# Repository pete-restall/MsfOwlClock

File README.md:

# MSF Owl Clock
<span style="display:block;text-align:center"></span>

The board with the ferrite rod antenna and two TFT displays attached.

The above images are the boards as delivered from fabrication, not the end product.  Namely:
* The edge / tool rails need to be cut off to leave only the owl-shaped board
* A ferrite rod antenna (and tuning capacitors) need to be attached, creating a branch on which the owl perches (yellow tie-wraps for talons)
* Two TFT displays need to be secured in place for the eyes
* A base / stand needs to be 3D printed, which will also hold a speaker and its cavity

This project is a desk clock intended to synchronise with the [60kHz AM MSF](doc/datasheets/msf/msf.pdf) time signal that is broadcast by the UK's NPL using their [Anthorn Radio Station in Cumbria, England](https://www.npl.co.uk/msf-signal).

The [board schematics](src/schematics/msf-owl-clock.pdf) and [PCB fab files](src/pcb-fab/) were created in KiCAD.  [Firmware](src/firmware/) will, no doubt, be a very long-running part of the project (as usually seems to happen...)

The board consists of:
* A [PIC32CX1025SG41100](doc/datasheets/mcu/PIC32CX1025SG41100-datasheet-DS60001715.pdf) ARM Cortex M4F:
  * M-profile ARM v7 CPU running up to 120MHz
  * 1MiB flash
  * 256KiB SRAM
  * 8KiB backup SRAM
  * 1Msps 12-bit ADC
  * 1Msps 12-bit DAC
* Two multiplexed QSPI [360x360 Circular TFTs](doc/datasheets/tft/buydisplay-ER-TFT1.32-1.pdf) for the eyes
* A USB Type-C connector with USB PD / charger detection and USB2.0 Full Speed data
* A Micro SD Card connector
* An [IS31AP4991A](doc/datasheets/opamps/IS31AP4991A-SLS2-TR.pdf) audio amplifier / speaker driver (the speaker and cavity will be built into a 3D-printed base / stand)
* A [BC805M](doc/datasheets/bluetooth/BC805M.pdf) 2.4GHz Bluetooth / BLE 5.2 Module running an [nRF52805](doc/datasheets/bluetooth/nRF52805_PS_v1.4.pdf) ARM Cortex M4
* A range of I<sup>2</sup>C sensors:
  * A [DPS310XTSA1](doc/datasheets/sensors/pressure/DPS310XTSA1.pdf) Pressure Sensor to create a barometer
  * A [HDC3022](doc/datasheets/sensors/humidity/HDC3022.pdf) Humidity Sensor for measuring humidity and temperature
  * A [VL6180V1NR](doc/datasheets/sensors/proximity/VL6180V1NR-1.pdf) Proximity Sensor to allow power-saving mode when nobody is nearby / at night
  * A [TSOP75338TT](doc/datasheets/sensors/infrared/TSOP75338TT.pdf) 38kHz Infrared Receiver to allow remote control

The board is shaped as an owl as it is intended for my daughter, a little girl that _really_ likes owls.  I hope it will spark some curiosity and prompt her to enquire how everyday items and systems around her work, things that most people take for granted or do not even notice.

Obviously it's also for me to play with, as and when I get the time.

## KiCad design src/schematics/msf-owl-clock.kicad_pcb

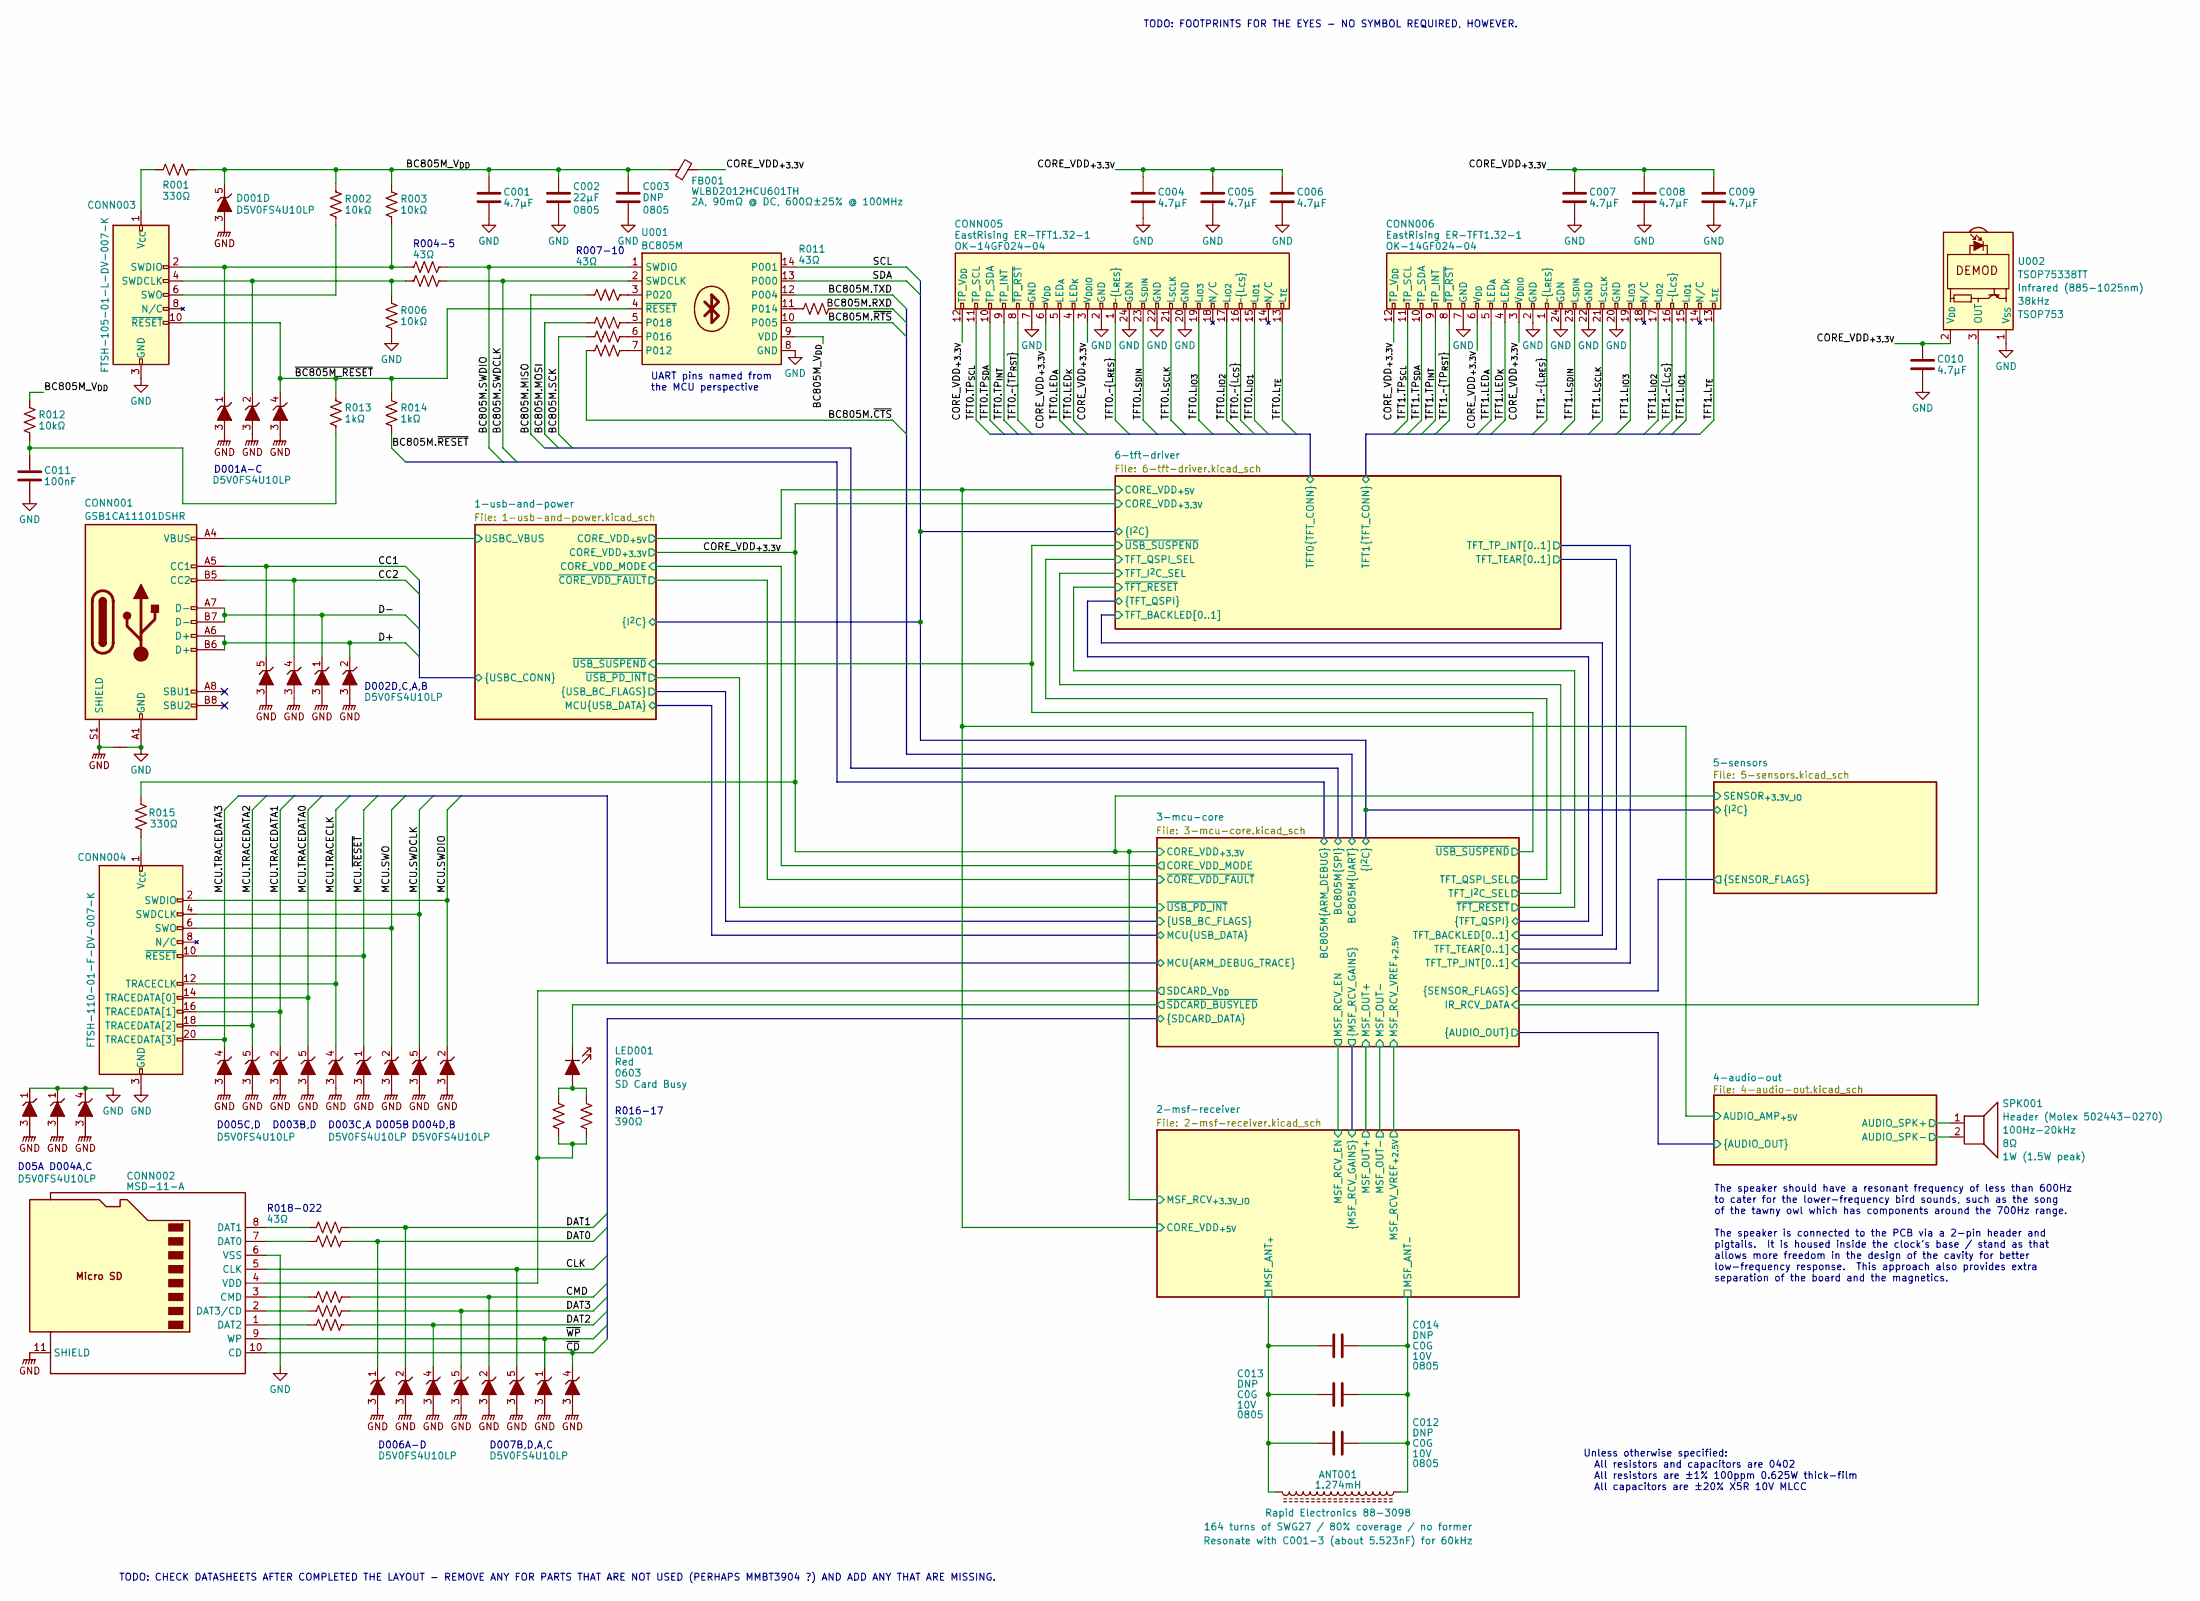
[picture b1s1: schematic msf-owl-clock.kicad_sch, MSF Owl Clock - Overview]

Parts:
ANT001: 1.274mH; ferrite-rod-antenna; ManufacturerPartNumber Rapid Electronics 88-3098
C001, C004, C005, C006, C007, C008, C009, C010: 4.7μF; unpolarised-nominal-0402-1005; Tolerance ±20%; VoltageRating 10V; ManufacturerPartNumber CL05A475MP5NRNC
C002: 22μF; unpolarised-nominal-0805-2012; Tolerance ±20%; VoltageRating 10V; ManufacturerPartNumber CL21A226MPQNNN
C003: DNP; unpolarised-nominal-0805-2012; Tolerance ±20%; VoltageRating 10V; ManufacturerPartNumber CL21A226MPQNNN
C011: 100nF; unpolarised-nominal-0402-1005; Tolerance ±20%; VoltageRating 10V; ManufacturerPartNumber CL05B104KA5NNNC
C012, C013, C014: DNP; unpolarised-nominal-0805-2012; VoltageRating 10V
CONN001: GSB1CA11101DSHR; ManufacturerPartNumber GSB1CA11101DSHR
CONN002: MSD-11-A; ManufacturerPartNumber MSD-11-A
CONN003: Cortex-M Debug Header; FTSH-105-?-?-DV-007-?-?; ManufacturerPartNumber FTSH-105-01-L-DV-007-K
CONN004: Cortex-M Debug Header with ETM; FTSH-110-01-?-DV-007-?-?; ManufacturerPartNumber FTSH-110-01-F-DV-007-K
CONN005, CONN006: EastRising ER-TFT1.32-1; OK-14GF024-04; ManufacturerPartNumber OK-14GF024-04
D001, D002, D003, D004, D005, D006, D007: D5V0FS4U10LP; ManufacturerPartNumber D5V0FS4U10LP
FB001: WLBD2012HCU601TH; WLBD2012; Tolerance ±25%; ManufacturerPartNumber WLBD2012HCU601TH
LED001: SD Card Busy; nominal-0603-1608; ManufacturerPartNumber B1931USD-20D000814U1930
NT001: Net Tie; net-tie-2-6mil
R001, R015: 330Ω; nominal-0402-1005; Tolerance ±1%; ManufacturerPartNumber WR04X3300FTL
R002, R003, R006, R012: 10kΩ; nominal-0402-1005; Tolerance ±1%; ManufacturerPartNumber WR04X1002FTL
R004, R005, R007, R008, R009, R010, R011, R018, R019, R020, R021, R022: 43Ω; nominal-0402-1005; Tolerance ±1%; ManufacturerPartNumber RC0402FR-0743RL
R013, R014: 1kΩ; nominal-0402-1005; Tolerance ±1%; ManufacturerPartNumber WR04X1001FTL
R016, R017: 390Ω; nominal-0402-1005; Tolerance ±1%; ManufacturerPartNumber RC0402FR-07390RL
SHEET001, SHEET002, SHEET003, SHEET004, SHEET005, SHEET006: (no value)
SPK001: Header (Molex 502443-0270); 502443-0270; Rating 1W (1.5W peak); ManufacturerPartNumber AC0402DR-0716KL
U001: BC805M; ManufacturerPartNumber BC805M
U002: TSOP75338TT; TSOP7????TT; ManufacturerPartNumber TSOP75338TT

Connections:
/1-usb-and-power/CC1: CONN001.A5 (CC1), D002.5 (K), D002.6; also elsewhere on the board
/1-usb-and-power/CC2: CONN001.B5 (CC2), D002.4 (K), D002.7; also elsewhere on the board
/1-usb-and-power/CORE_VDD_{+5V}: CONN005.5 (LED_{A}), CONN006.5 (LED_{A}); also elsewhere on the board
/1-usb-and-power/D+: CONN001.A6 (D+), CONN001.B6 (D+), D002.2 (K), D002.9; also elsewhere on the board
/1-usb-and-power/D-: CONN001.A7 (D-), CONN001.B7 (D-), D002.1 (K), D002.10; also elsewhere on the board
/1-usb-and-power/SCL: U001.14 (P001); also elsewhere on the board
/1-usb-and-power/SDA: U001.13 (P000); also elsewhere on the board
/1-usb-and-power/USBC_VBUS: CONN001.A4 (VBUS), CONN001.A9 (VBUS), CONN001.B4 (VBUS), CONN001.B9 (VBUS); also elsewhere on the board
/2-msf-receiver/MSF_ANT_{+}: ANT001.1, C012.1, C013.1, C014.1; also elsewhere on the board
/2-msf-receiver/MSF_RCV_VREF_{+1.8V}: ANT001.2, C012.2, C013.2, C014.2; also elsewhere on the board
/3-mcu-core/BC805M.MISO: R007.1; also elsewhere on the board
/3-mcu-core/BC805M.MOSI: R008.1; also elsewhere on the board
/3-mcu-core/BC805M.RXD: R011.2; also elsewhere on the board
/3-mcu-core/BC805M.SCK: R009.1; also elsewhere on the board
/3-mcu-core/BC805M.SWDCLK: R005.2, U001.2 (SWDCLK); also elsewhere on the board
/3-mcu-core/BC805M.SWDIO: R004.2, U001.1 (SWDIO); also elsewhere on the board
/3-mcu-core/BC805M.TXD: U001.12 (P004); also elsewhere on the board
/3-mcu-core/BC805M.~CTS: R010.1; also elsewhere on the board
/3-mcu-core/BC805M.~RESET: R014.2; also elsewhere on the board
/3-mcu-core/BC805M.~RTS: U001.10 (P005); also elsewhere on the board
/3-mcu-core/CLK: CONN002.5 (CLK), D007.5 (K), D007.6; also elsewhere on the board
/3-mcu-core/CMD: D007.2 (K), D007.9, R020.2; also elsewhere on the board
/3-mcu-core/DAT0: D006.1 (K), D006.10, R019.2; also elsewhere on the board
/3-mcu-core/DAT1: D006.2 (K), D006.9, R018.2; also elsewhere on the board
/3-mcu-core/DAT2: D006.4 (K), D006.7, R022.2; also elsewhere on the board
/3-mcu-core/DAT3: D006.5 (K), D006.6, R021.2; also elsewhere on the board
/3-mcu-core/IR_RCV_DATA: U002.3 (OUT); also elsewhere on the board
/3-mcu-core/MCU.SWDCLK: CONN004.4 (SWDCLK), D004.5 (K), D004.6; also elsewhere on the board
/3-mcu-core/MCU.SWDIO: CONN004.2 (SWDIO), D004.2 (K), D004.9; also elsewhere on the board
/3-mcu-core/MCU.SWO: CONN004.6 (SWO), D005.2 (K), D005.9; also elsewhere on the board
/3-mcu-core/MCU.TRACECLK: CONN004.12 (TRACECLK), D003.4 (K), D003.7; also elsewhere on the board
/3-mcu-core/MCU.TRACEDATA0: CONN004.14 (TRACEDATA[0]), D003.5 (K), D003.6; also elsewhere on the board
/3-mcu-core/MCU.TRACEDATA1: CONN004.16 (TRACEDATA[1]), D003.2 (K), D003.9; also elsewhere on the board
/3-mcu-core/MCU.TRACEDATA2: CONN004.18 (TRACEDATA[2]), D005.5 (K), D005.6; also elsewhere on the board
/3-mcu-core/MCU.TRACEDATA3: CONN004.20 (TRACEDATA[3]), D005.4 (K), D005.7; also elsewhere on the board
/3-mcu-core/MCU.~RESET: CONN004.10 (~RESET), D003.1 (K), D003.10; also elsewhere on the board
/3-mcu-core/SDCARD_V_{DD}: CONN002.4 (VDD), R016.2, R017.2; also elsewhere on the board
/3-mcu-core/~CD: CONN002.10 (CD), D007.4 (K), D007.7; also elsewhere on the board
/3-mcu-core/~SDCARD_BUSYLED: LED001.1 (K); also elsewhere on the board
/3-mcu-core/~WP: CONN002.9 (WP), D007.1 (K), D007.10; also elsewhere on the board
/4-audio-out/AUDIO_SPK+: SPK001.1; also elsewhere on the board
/4-audio-out/AUDIO_SPK-: SPK001.2; also elsewhere on the board
/6-tft-driver/TFT0.LED_{K}: CONN005.4 (LED_{K}); also elsewhere on the board
/6-tft-driver/TFT0.L_{IO1}: CONN005.15 (L_{IO1}); also elsewhere on the board
/6-tft-driver/TFT0.L_{IO2}: CONN005.17 (L_{IO2}); also elsewhere on the board
/6-tft-driver/TFT0.L_{IO3}: CONN005.19 (L_{IO3}); also elsewhere on the board
/6-tft-driver/TFT0.L_{SCLK}: CONN005.21 (L_{SCLK}); also elsewhere on the board
/6-tft-driver/TFT0.L_{SDIN}: CONN005.23 (L_{SDIN}); also elsewhere on the board
/6-tft-driver/TFT0.L_{TE}: CONN005.13 (L_{TE}); also elsewhere on the board
/6-tft-driver/TFT0.TP_{INT}: CONN005.9 (TP_INT); also elsewhere on the board
/6-tft-driver/TFT0.TP_{SCL}: CONN005.11 (TP_SCL); also elsewhere on the board
/6-tft-driver/TFT0.TP_{SDA}: CONN005.10 (TP_SDA); also elsewhere on the board
/6-tft-driver/TFT0.~L_{CS}: CONN005.16 (~L_{CS}); also elsewhere on the board
/6-tft-driver/TFT0.~L_{RES}: CONN005.1 (~L_{RES}); also elsewhere on the board
/6-tft-driver/TFT0.~TP_{RST}: CONN005.8 (~TP_RST); also elsewhere on the board
/6-tft-driver/TFT1.LED_{K}: CONN006.4 (LED_{K}); also elsewhere on the board
/6-tft-driver/TFT1.L_{IO1}: CONN006.15 (L_{IO1}); also elsewhere on the board
/6-tft-driver/TFT1.L_{IO2}: CONN006.17 (L_{IO2}); also elsewhere on the board
/6-tft-driver/TFT1.L_{IO3}: CONN006.19 (L_{IO3}); also elsewhere on the board
/6-tft-driver/TFT1.L_{SCLK}: CONN006.21 (L_{SCLK}); also elsewhere on the board
/6-tft-driver/TFT1.L_{SDIN}: CONN006.23 (L_{SDIN}); also elsewhere on the board
/6-tft-driver/TFT1.L_{TE}: CONN006.13 (L_{TE}); also elsewhere on the board
/6-tft-driver/TFT1.TP_{INT}: CONN006.9 (TP_INT); also elsewhere on the board
/6-tft-driver/TFT1.TP_{SCL}: CONN006.11 (TP_SCL); also elsewhere on the board
/6-tft-driver/TFT1.TP_{SDA}: CONN006.10 (TP_SDA); also elsewhere on the board
/6-tft-driver/TFT1.~L_{CS}: CONN006.16 (~L_{CS}); also elsewhere on the board
/6-tft-driver/TFT1.~L_{RES}: CONN006.1 (~L_{RES}); also elsewhere on the board
/6-tft-driver/TFT1.~TP_{RST}: CONN006.8 (~TP_RST); also elsewhere on the board
/BC805M_V_{DD}: C001.1, C002.1, C003.1, D001.5 (K), D001.6, FB001.1 (P1_PWROUT), R001.2, R002.1, R003.1, R012.1, U001.9 (VDD)
/CORE_VDD_{+3.3V}: C004.1, C005.1, C006.1, C007.1, C008.1, C009.1, C010.1, CONN005.3 (V_{DDIO}), CONN005.6 (V_{DD}), CONN005.12 (TP_V_{DD}), CONN006.3 (V_{DDIO}), CONN006.6 (V_{DD}), CONN006.12 (TP_V_{DD}), FB001.2 (P2_PWRIN), R015.2, U002.2 (V_{DD}); also elsewhere on the board
/~BC805M_RESET: CONN003.10 (~RESET), D001.4 (K), D001.7, R013.1, R014.1, U001.4 (~RESET)
unnamed: C011.1, R012.2, R013.2
unnamed: CONN002.3 (CMD), R020.1
unnamed: CONN002.7 (DAT0), R019.1
unnamed: CONN002.8 (DAT1), R018.1
unnamed: CONN002.1 (DAT2), R022.1
unnamed: CONN002.2 (DAT3/CD), R021.1
unnamed: CONN003.4 (SWDCLK), D001.2 (K), D001.9, R005.1, R006.1
unnamed: CONN003.2 (SWDIO), D001.1 (K), D001.10, R003.2, R004.1
unnamed: CONN003.6 (SWO), R002.2
unnamed: CONN003.1 (V_{CC}), R001.1
unnamed: CONN004.1 (V_{CC}), R015.1
unnamed: LED001.2 (A), R016.1, R017.1
unnamed: R010.2, U001.7 (P012)
unnamed: R011.1, U001.11 (P014)
unnamed: R009.2, U001.6 (P016)
unnamed: R008.2, U001.5 (P018)
unnamed: R007.2, U001.3 (P020)

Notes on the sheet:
D006A-D
D002D,C,A,B
D001A-C
D005B
TODO: CHECK DATASHEETS AFTER COMPLETED THE LAYOUT - REMOVE ANY FOR PARTS THAT ARE NOT USED (PERHAPS MMBT3904 ?) AND ADD ANY THAT ARE MISSING.
UART pins named from the MCU perspective
The speaker should have a resonant frequency of less than 600Hz to cater for the lower-frequency bird sounds, such as the song of the tawny owl which has components around the 700Hz range. The speaker is connected to the PCB via a 2-pin header and pigtails. It is housed inside the clock's base / st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
D003C,A
Unless otherwise specified: All resistors and capacitors are 0402 All resistors are ±1% 100ppm 0.625W thick-film All capacitors are ±20% X5R 10V MLCC
D003B,D
D004D,B
D007B,D,A,C
R016-17
TODO: FOOTPRINTS FOR THE EYES - NO SYMBOL REQUIRED, HOWEVER.
R018-022
R004-5
D05A D004A,C
R007-10
D005C,D

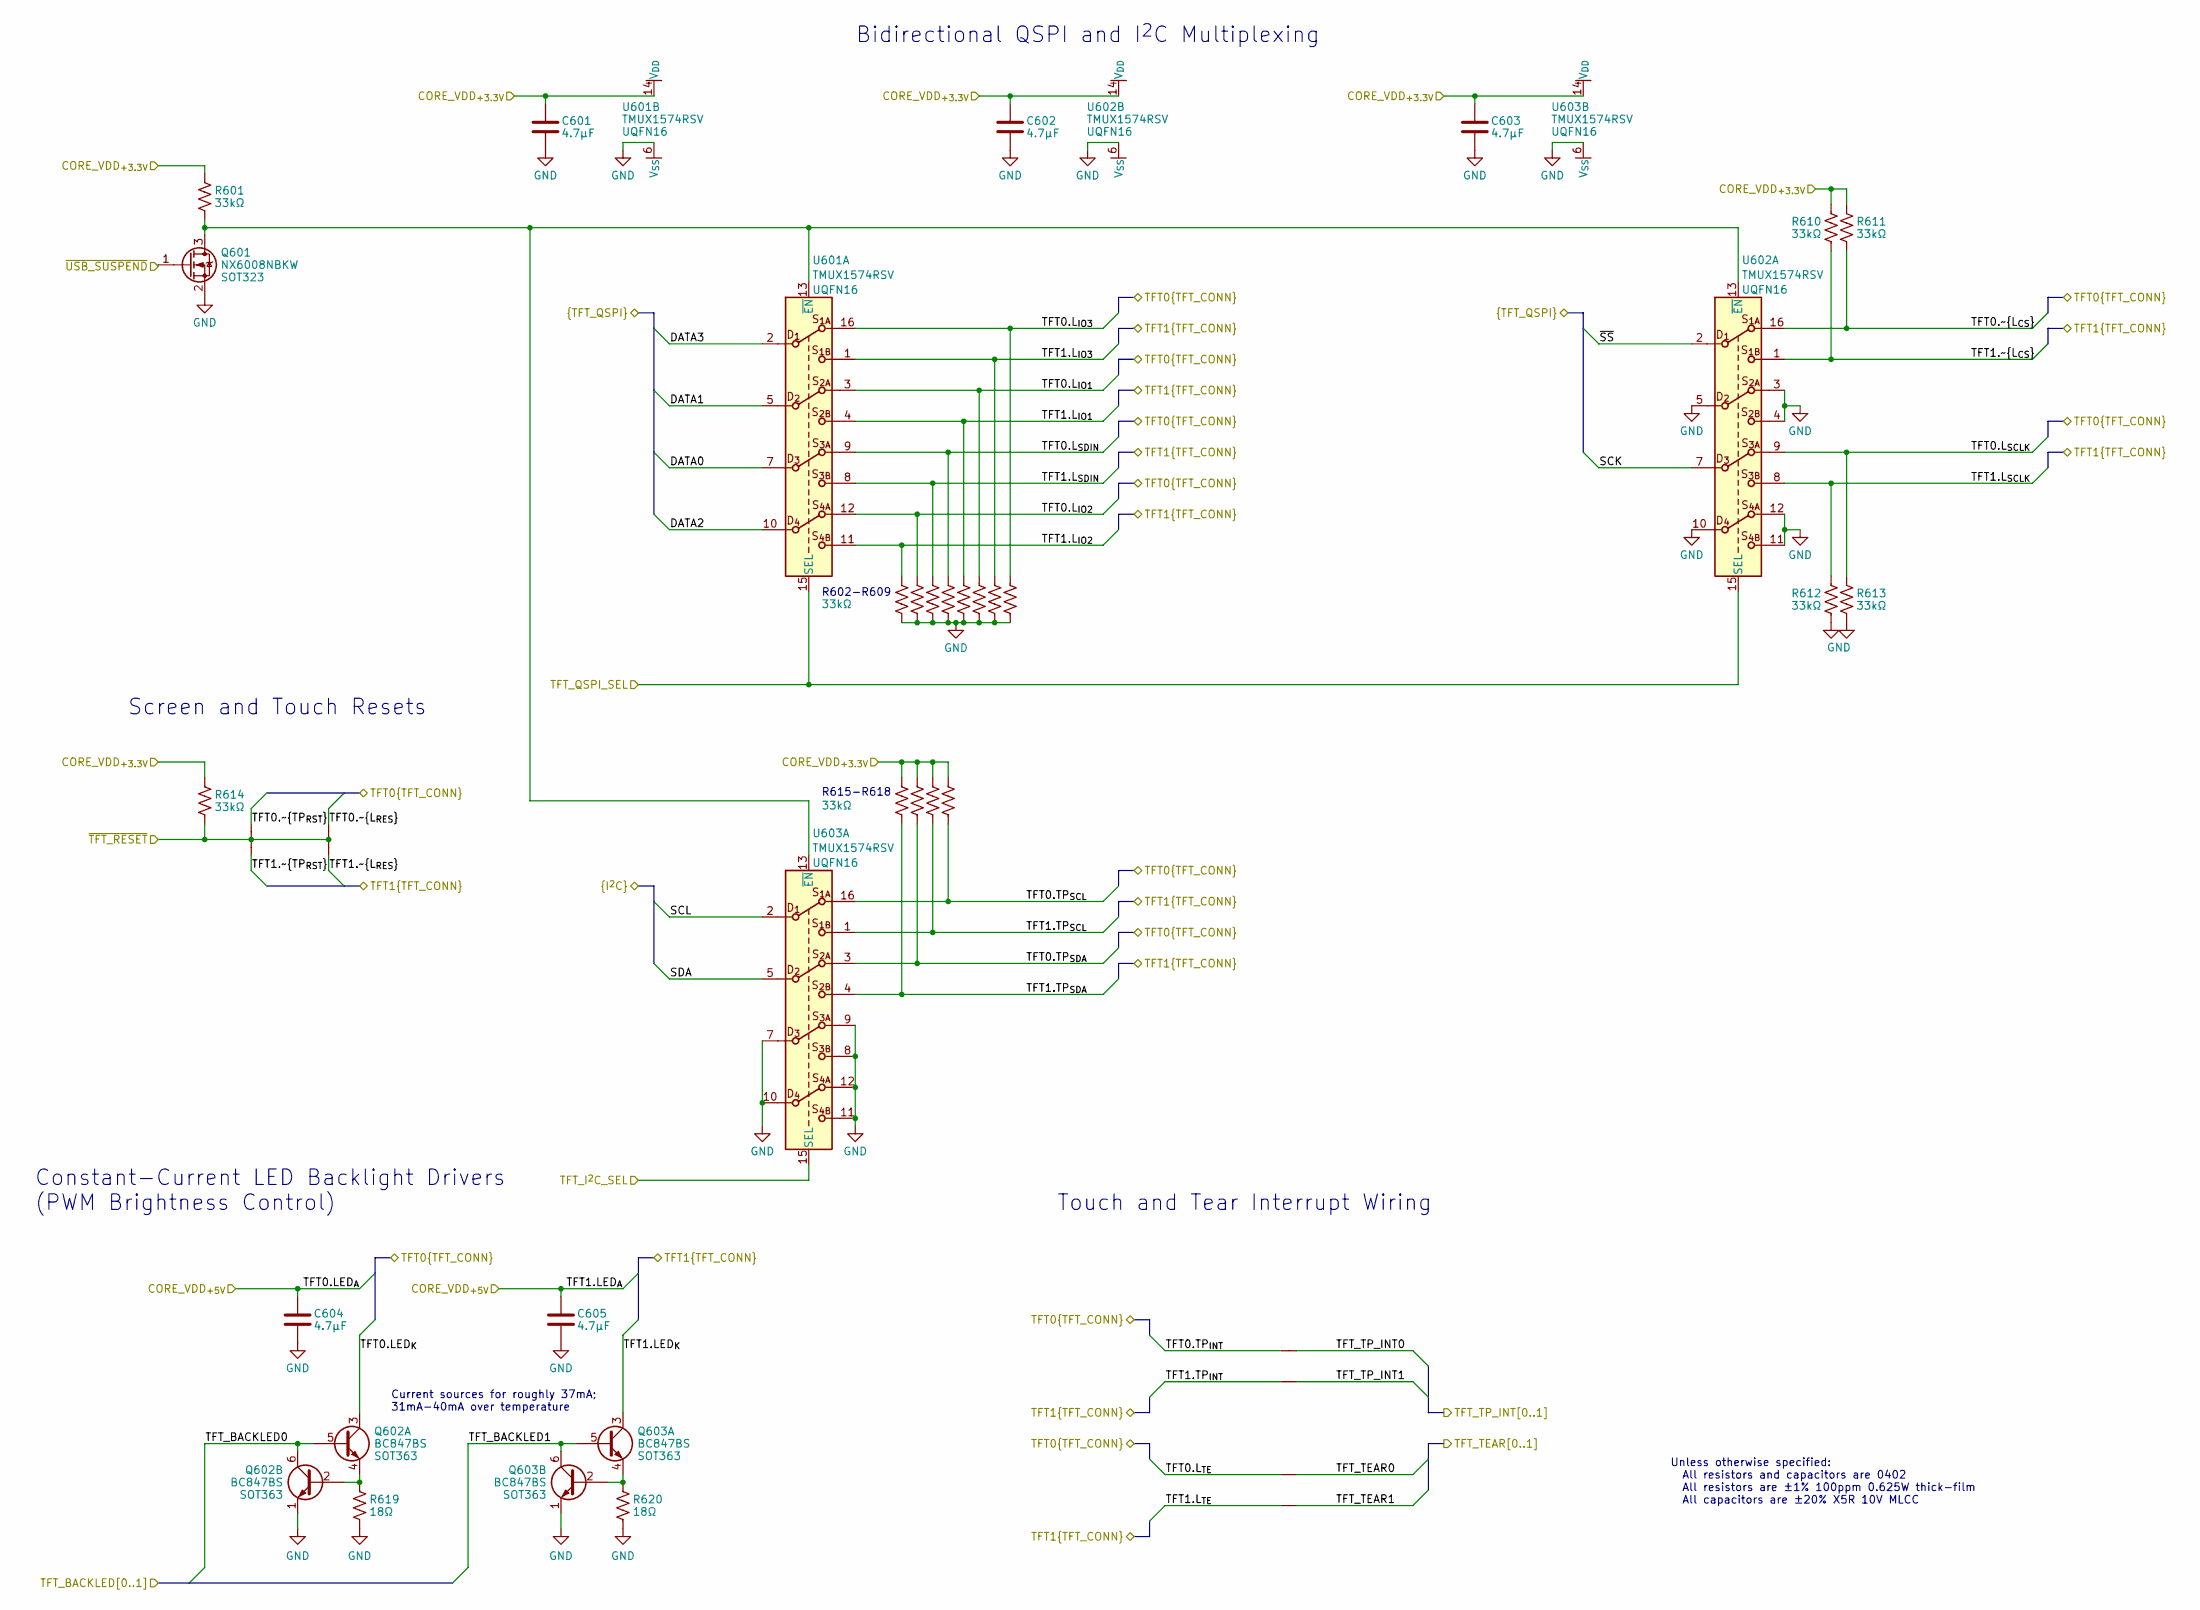
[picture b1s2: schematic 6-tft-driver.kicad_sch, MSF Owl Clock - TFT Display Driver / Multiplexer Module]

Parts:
C601, C602, C603, C604, C605: 4.7μF; unpolarised-nominal-0402-1005; Tolerance ±20%; VoltageRating 10V; ManufacturerPartNumber CL05A475MP5NRNC
NT601, NT602, NT603, NT604, NT605, NT606, NT607, NT608: Net Tie; net-tie-2-6mil
Q601: NX6008NBKW; SOT323; ManufacturerPartNumber NX6008NBKW
Q602, Q603: BC847BS; SOT363; ManufacturerPartNumber BC847BS-7-F
R601, R602, R603, R604, R605, R606, R607, R608, R609, R610, R611, R612, R613, R614, R615, R616, R617, R618: 33kΩ; nominal-0402-1005; Tolerance ±1%; ManufacturerPartNumber WR04X3302FTL
R619, R620: 18Ω; nominal-0402-1005; Tolerance ±1%; ManufacturerPartNumber RC0402FR-0718RL
U601, U602, U603: TMUX1574RSV; UQFN16-1.8x2.6mm-0.4mm; ManufacturerPartNumber TMUX1574RSVR

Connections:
/1-usb-and-power/CORE_VDD_{+5V}: C604.1, C605.1; also elsewhere on the board
/1-usb-and-power/SCL: U603.2; also elsewhere on the board
/1-usb-and-power/SDA: U603.5; also elsewhere on the board
/1-usb-and-power/~USB_SUSPEND: Q601.1 (G); also elsewhere on the board
/3-mcu-core/DATA0: U601.7; also elsewhere on the board
/3-mcu-core/DATA1: U601.5; also elsewhere on the board
/3-mcu-core/DATA2: U601.10; also elsewhere on the board
/3-mcu-core/DATA3: U601.2; also elsewhere on the board
/3-mcu-core/SCK: U602.7; also elsewhere on the board
/3-mcu-core/TFT_BACKLED0: Q602.5 (B), Q602.6 (C); also elsewhere on the board
/3-mcu-core/TFT_BACKLED1: Q603.5 (B), Q603.6 (C); also elsewhere on the board
/3-mcu-core/TFT_I^{2}C_SEL: U603.15 (SEL); also elsewhere on the board
/3-mcu-core/TFT_QSPI_SEL: U601.15 (SEL), U602.15 (SEL); also elsewhere on the board
/3-mcu-core/TFT_TEAR0: NT603.2 (P2_OUT); also elsewhere on the board
/3-mcu-core/TFT_TEAR1: NT604.2 (P2_OUT); also elsewhere on the board
/3-mcu-core/TFT_TP_INT0: NT601.2 (P2_OUT); also elsewhere on the board
/3-mcu-core/TFT_TP_INT1: NT602.2 (P2_OUT); also elsewhere on the board
/3-mcu-core/~SS: U602.2; also elsewhere on the board
/3-mcu-core/~TFT_RESET: NT605.1 (P1_IN), NT606.1 (P1_IN), NT607.1 (P1_IN), NT608.1 (P1_IN), R614.2; also elsewhere on the board
/6-tft-driver/TFT0.LED_{K}: Q602.3 (C); also elsewhere on the board
/6-tft-driver/TFT0.L_{IO1}: R607.1, U601.3; also elsewhere on the board
/6-tft-driver/TFT0.L_{IO2}: R603.1, U601.12; also elsewhere on the board
/6-tft-driver/TFT0.L_{IO3}: R609.1, U601.16; also elsewhere on the board
/6-tft-driver/TFT0.L_{SCLK}: R613.1, U602.9; also elsewhere on the board
/6-tft-driver/TFT0.L_{SDIN}: R605.1, U601.9; also elsewhere on the board
/6-tft-driver/TFT0.L_{TE}: NT603.1 (P1_IN); also elsewhere on the board
/6-tft-driver/TFT0.TP_{INT}: NT601.1 (P1_IN); also elsewhere on the board
/6-tft-driver/TFT0.TP_{SCL}: R618.2, U603.16; also elsewhere on the board
/6-tft-driver/TFT0.TP_{SDA}: R616.2, U603.3; also elsewhere on the board
/6-tft-driver/TFT0.~L_{CS}: R611.2, U602.16; also elsewhere on the board
/6-tft-driver/TFT0.~L_{RES}: NT607.2 (P2_OUT); also elsewhere on the board
/6-tft-driver/TFT0.~TP_{RST}: NT605.2 (P2_OUT); also elsewhere on the board
/6-tft-driver/TFT1.LED_{K}: Q603.3 (C); also elsewhere on the board
/6-tft-driver/TFT1.L_{IO1}: R606.1, U601.4; also elsewhere on the board
/6-tft-driver/TFT1.L_{IO2}: R602.1, U601.11; also elsewhere on the board
/6-tft-driver/TFT1.L_{IO3}: R608.1, U601.1; also elsewhere on the board
/6-tft-driver/TFT1.L_{SCLK}: R612.1, U602.8; also elsewhere on the board
/6-tft-driver/TFT1.L_{SDIN}: R604.1, U601.8; also elsewhere on the board
/6-tft-driver/TFT1.L_{TE}: NT604.1 (P1_IN); also elsewhere on the board
/6-tft-driver/TFT1.TP_{INT}: NT602.1 (P1_IN); also elsewhere on the board
/6-tft-driver/TFT1.TP_{SCL}: R617.2, U603.1; also elsewhere on the board
/6-tft-driver/TFT1.TP_{SDA}: R615.2, U603.4; also elsewhere on the board
/6-tft-driver/TFT1.~L_{CS}: R610.2, U602.1; also elsewhere on the board
/6-tft-driver/TFT1.~L_{RES}: NT608.2 (P2_OUT); also elsewhere on the board
/6-tft-driver/TFT1.~TP_{RST}: NT606.2 (P2_OUT); also elsewhere on the board
/CORE_VDD_{+3.3V}: C601.1, C602.1, C603.1, R601.1, R610.1, R611.1, R614.1, R615.1, R616.1, R617.1, R618.1, U601.14 (V_{DD}), U602.14 (V_{DD}), U603.14 (V_{DD}); also elsewhere on the board
unnamed: Q601.3 (D), R601.2, U601.13 (~EN), U602.13 (~EN), U603.13 (~EN)
unnamed: Q602.2 (B), Q602.4 (E), R619.1
unnamed: Q603.2 (B), Q603.4 (E), R620.1

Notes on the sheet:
Screen and Touch Resets
R615-R618
R602-R609
Constant-Current LED Backlight Drivers (PWM Brightness Control)
Current sources for roughly 37mA; 31mA-40mA over temperature
Bidirectional QSPI and I^{2}C Multiplexing
Touch and Tear Interrupt Wiring
Unless otherwise specified: All resistors and capacitors are 0402 All resistors are ±1% 100ppm 0.625W thick-film All capacitors are ±20% X5R 10V MLCC

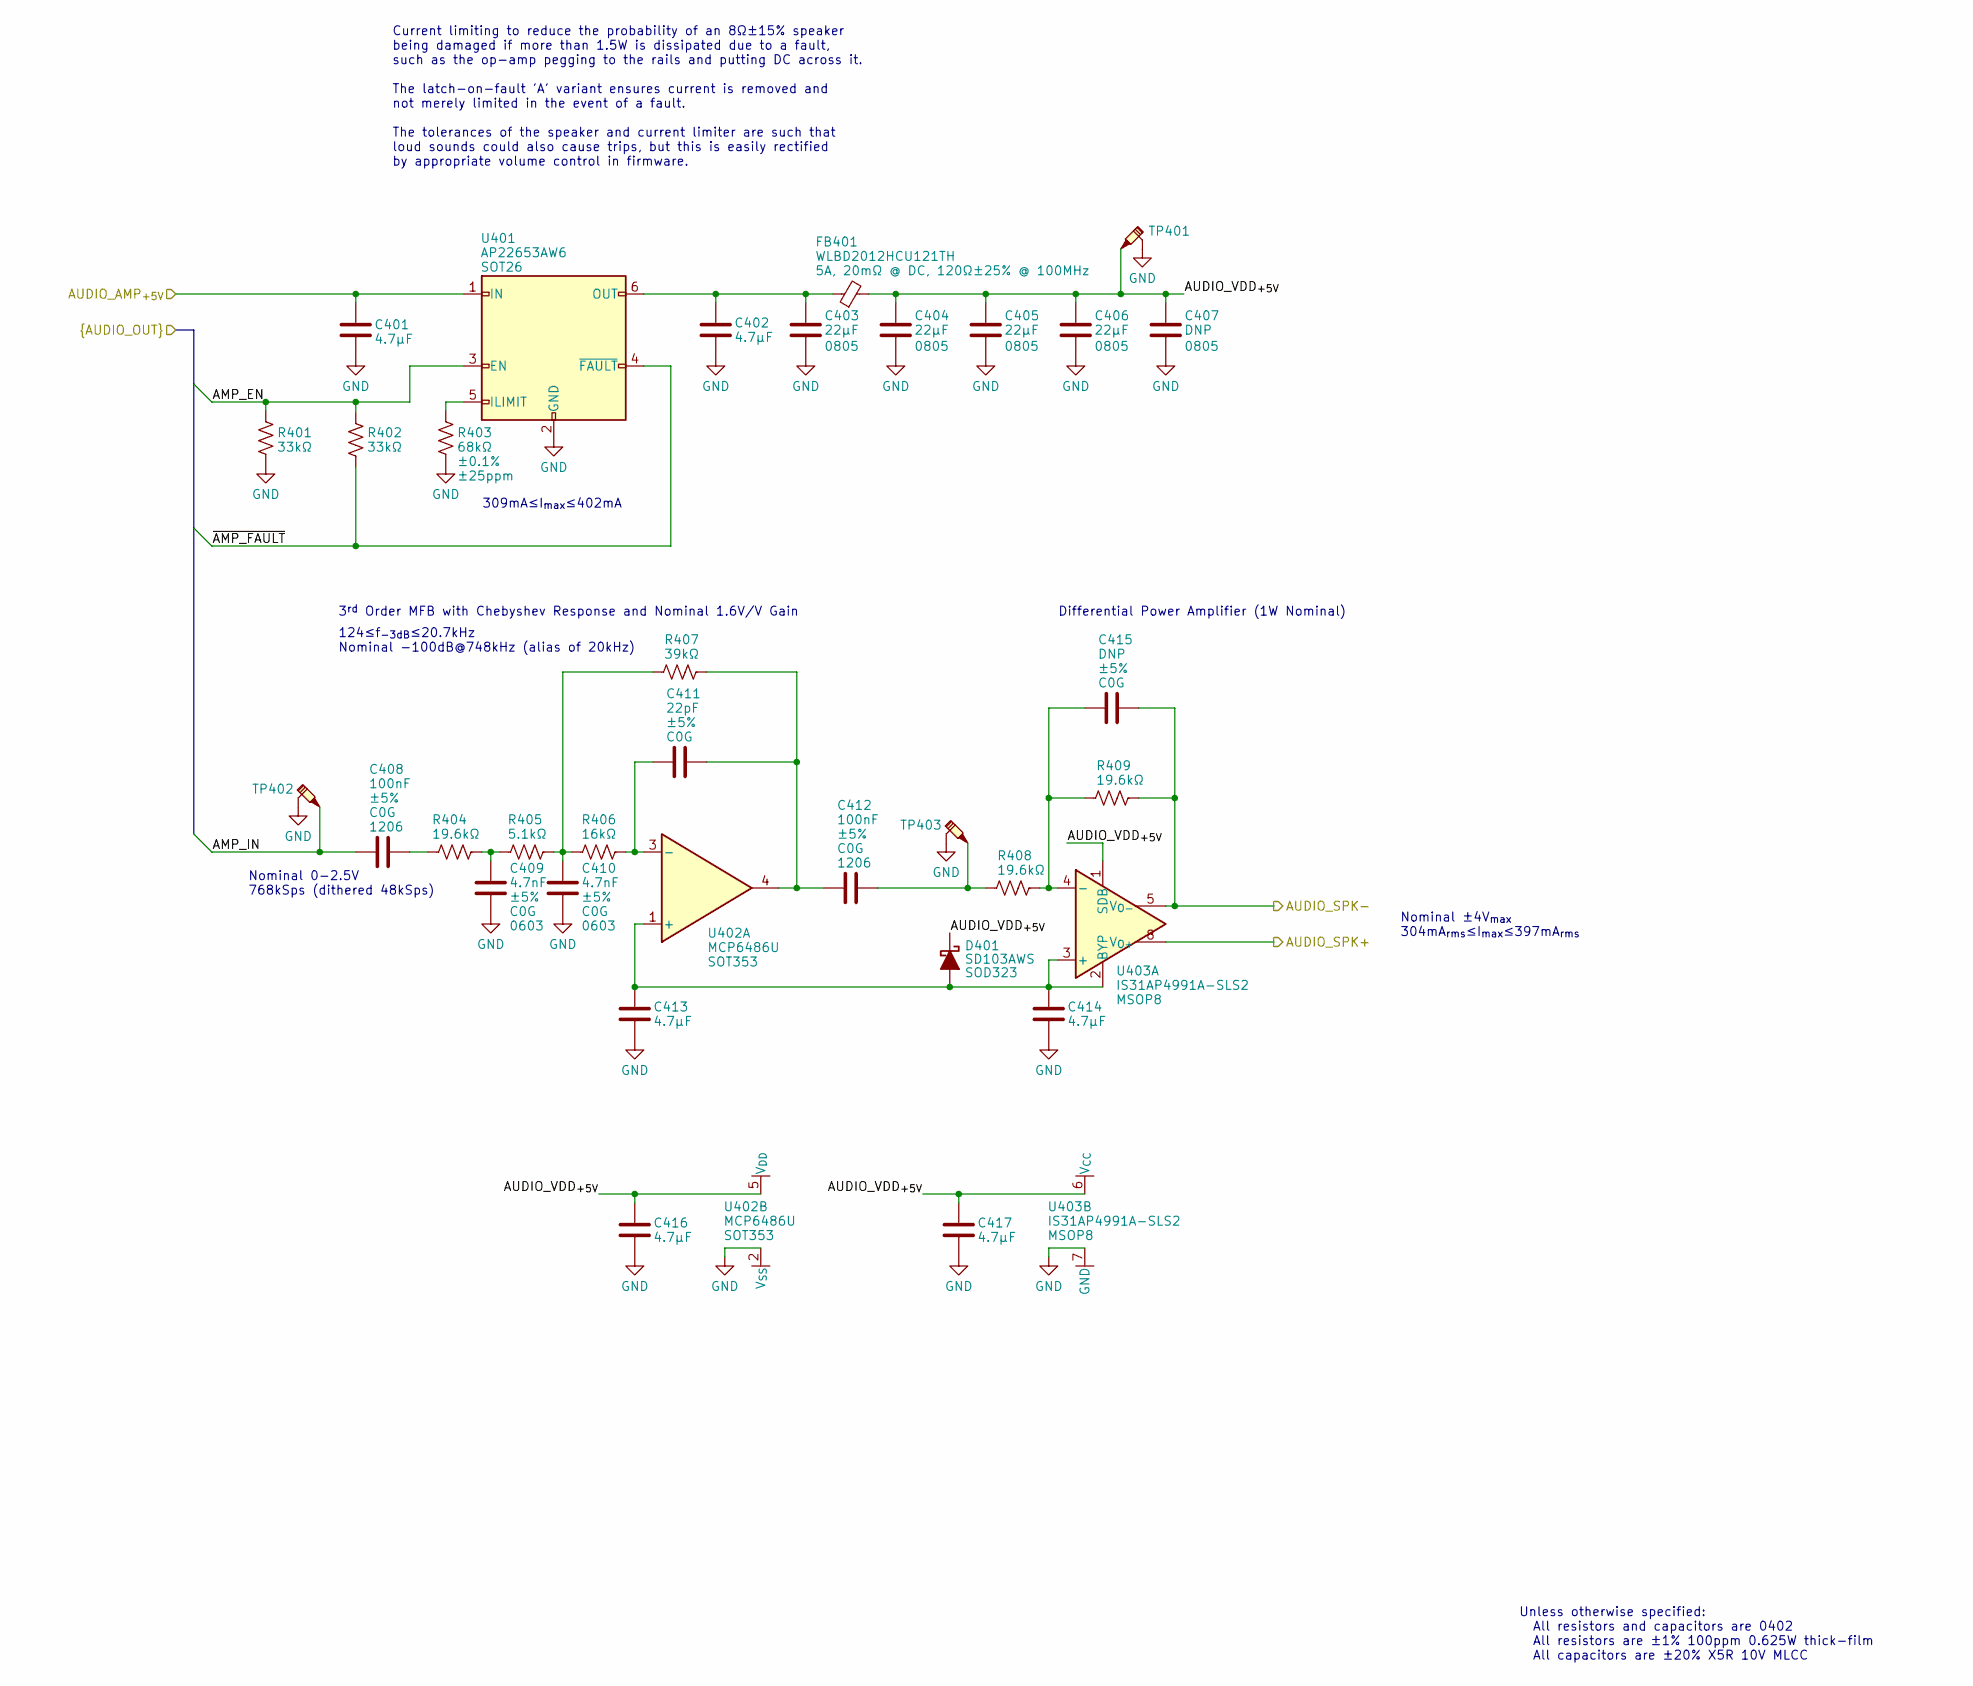
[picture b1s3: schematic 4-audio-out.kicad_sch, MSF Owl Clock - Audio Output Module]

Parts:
C401, C402, C413, C414, C416, C417: 4.7μF; unpolarised-nominal-0402-1005; Tolerance ±20%; VoltageRating 10V; ManufacturerPartNumber CL05A475MP5NRNC
C403, C404, C405, C406: 22μF; unpolarised-nominal-0805-2012; Tolerance ±20%; VoltageRating 10V; ManufacturerPartNumber CL21A226MPQNNN
C407: DNP; unpolarised-nominal-0805-2012; Tolerance ±20%; VoltageRating 10V; ManufacturerPartNumber CL21A226MPQNNN
C408, C412: 100nF; unpolarised-nominal-1206-3216; Tolerance ±5%; VoltageRating 10V; ManufacturerPartNumber GRM3195C1H104JA05D
C409, C410: 4.7nF; unpolarised-nominal-0603-1608; Tolerance ±5%; VoltageRating 10V; ManufacturerPartNumber CC0603FRNPO9BN472
C411: 22pF; unpolarised-nominal-0402-1005; Tolerance ±5%; VoltageRating 10V; ManufacturerPartNumber GCM1555C1H220FA16D
C415: DNP; unpolarised-nominal-0402-1005; Tolerance ±5%; VoltageRating 10V
D401: SD103AWS; SOD323; ManufacturerPartNumber SD103AWS
FB401: WLBD2012HCU121TH; WLBD2012; Tolerance ±25%; ManufacturerPartNumber WLBD2012HCU121TH
R401, R402: 33kΩ; nominal-0402-1005; Tolerance ±1%; ManufacturerPartNumber WR04X3302FTL
R403: 68kΩ; nominal-0402-1005; Tolerance ±0.1%; ManufacturerPartNumber RN73R1ETTP6802B25
R404, R408, R409: 19.6kΩ; nominal-0402-1005; Tolerance ±1%; ManufacturerPartNumber WR04X1962FTL
R405: 5.1kΩ; nominal-0402-1005; Tolerance ±1%; ManufacturerPartNumber WR04X5101FTL
R406: 16kΩ; nominal-0402-1005; Tolerance ±1%; ManufacturerPartNumber AC0402DR-0716KL
R407: 39kΩ; nominal-0402-1005; Tolerance ±1%; ManufacturerPartNumber RC0402FR-0739KL
TP401, TP402, TP403: testpoint-SP3050A-with-short-gnd
U401: AP22653AW6; SOT26; ManufacturerPartNumber AP22653AW6-7
U402: MCP6486U; SOT353; ManufacturerPartNumber MCP6486UT-E-LT
U403: IS31AP4991A-SLS2; MSOP8-3x3mm-0.65mm; ManufacturerPartNumber IS31AP4991A-SLS2-TR

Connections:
/1-usb-and-power/CORE_VDD_{+5V}: C401.1, U401.1 (IN); also elsewhere on the board
/3-mcu-core/AMP_EN: R401.1, R402.1, U401.3 (EN); also elsewhere on the board
/3-mcu-core/AMP_IN: C408.1, TP402.1; also elsewhere on the board
/3-mcu-core/~AMP_FAULT: R402.2, U401.4 (~FAULT); also elsewhere on the board
/4-audio-out/AUDIO_SPK+: U403.8 (V_{O+}); also elsewhere on the board
/4-audio-out/AUDIO_SPK-: C415.2, R409.2, U403.5 (V_{O-}); also elsewhere on the board
/4-audio-out/AUDIO_VDD_{+5V}: C404.1, C405.1, C406.1, C407.1, C416.1, C417.1, D401.1 (K), FB401.2 (P2_PWROUT), TP401.1, U402.5 (V_{DD}), U403.1 (SDB), U403.6 (V_{CC})
unnamed: C408.2, R404.1
unnamed: C409.2, R404.2, R405.1
unnamed: C410.2, R405.2, R406.1, R407.1
unnamed: C411.2, C412.1, R407.2, U402.4
unnamed: C412.2, R408.1, TP403.1
unnamed: C413.1, C414.1, D401.2 (A), U402.1 (+), U403.2 (BYP), U403.3 (+)
unnamed: C402.1, C403.1, FB401.1 (P1_PWRIN), U401.6 (OUT)
unnamed: R403.1, U401.5 (ILIMIT)
unnamed: C411.1, R406.2, U402.3 (-)
unnamed: C415.1, R408.2, R409.1, U403.4 (-)

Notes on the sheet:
Differential Power Amplifier (1W Nominal)
3^{rd} Order MFB with Chebyshev Response and Nominal 1.6V/V Gain
Nominal ±4V_{max} 304mA_{rms}≤I_{max}≤397mA_{rms}
Current limiting to reduce the probability of an 8Ω±15% speaker being damaged if more than 1.5W is dissipated due to a fault, such as the op-amp pegging to the rails and putting DC across it. The latch-on-fault 'A' variant ensures current is removed and not merely limited in the event of a fault. T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
124≤f_{-3dB}≤20.7kHz Nominal -100dB@748kHz (alias of 20kHz)
Nominal 0-2.5V 768kSps (dithered 48kSps)
Unless otherwise specified: All resistors and capacitors are 0402 All resistors are ±1% 100ppm 0.625W thick-film All capacitors are ±20% X5R 10V MLCC
309mA≤I_{max}≤402mA
